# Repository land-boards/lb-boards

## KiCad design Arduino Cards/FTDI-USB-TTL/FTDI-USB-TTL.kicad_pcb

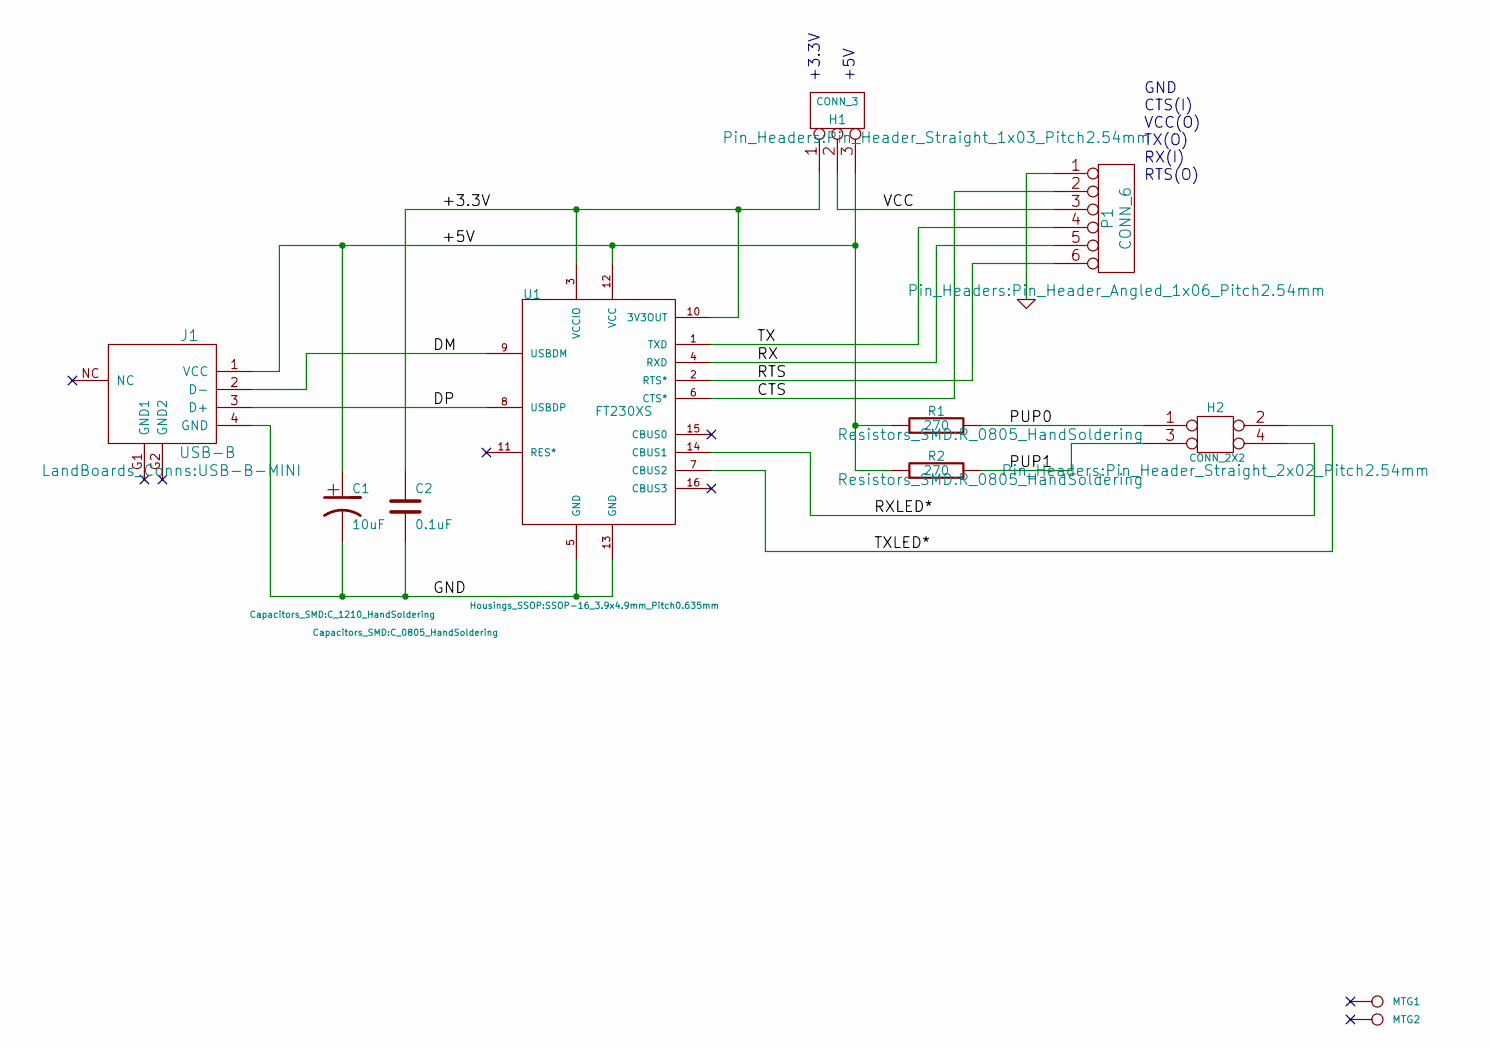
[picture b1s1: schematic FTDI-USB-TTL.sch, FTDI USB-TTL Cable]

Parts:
C1: 10uF; C_1210_HandSoldering; MfgPN CC121ZKY5V8BB106
C2: 0.1uF; C_0805_HandSoldering; MfgPN GRM155F51E104ZA1J
H1: CONN_3; Pin_Header_Straight_1x03_Pitch2.54mm; MfgPN 68002-103HLF
H2: CONN_2X2; Pin_Header_Straight_2x02_Pitch2.54mm
J1: USB-B; USB-B-MINI; MfgPN UX60SC-MB-5ST(80)
MTG1: CONN_1; MTG-4-40; MfgPN N/A
MTG2: CONN_1; MTG-4-40
P1: CONN_6; Pin_Header_Angled_1x06_Pitch2.54mm; MfgPN 68002-106HLF
R1: 270; R_0805_HandSoldering; MfgPN CRG0805F270R
R2: 270; R_0805_HandSoldering
U1: FT230XS; SSOP-16_3.9x4.9mm_Pitch0.635mm

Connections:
/+3.3V: C2.1, H1.1, U1.3 (VCCIO), U1.10 (3V3OUT)
/+5V: C1.1, H1.3, J1.1 (VCC), R1.1, R2.1, U1.12 (VCC)
/CTS: P1.2, U1.6 (CTS*)
/DM: J1.2 (D-), U1.9 (USBDM)
/DP: J1.3 (D+), U1.8 (USBDP)
/PUP0: H2.1, R1.2
/PUP1: H2.3, R2.2
/RTS: P1.6, U1.2 (RTS*)
/RX: P1.5, U1.4 (RXD)
/RXLED*: H2.4, U1.14 (CBUS1)
/TX: P1.4, U1.1 (TXD)
/TXLED*: H2.2, U1.7 (CBUS2)
/VCC: H1.2 (PM), P1.3
GND: C1.2, C2.2, J1.4 (GND), P1.1, U1.5 (GND), U1.13 (GND)

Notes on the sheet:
GND CTS(I) VCC(O) TX(O) RX(I) RTS(O)
+3.3V +5V

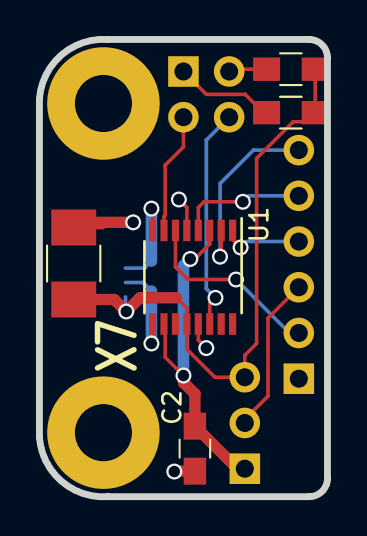
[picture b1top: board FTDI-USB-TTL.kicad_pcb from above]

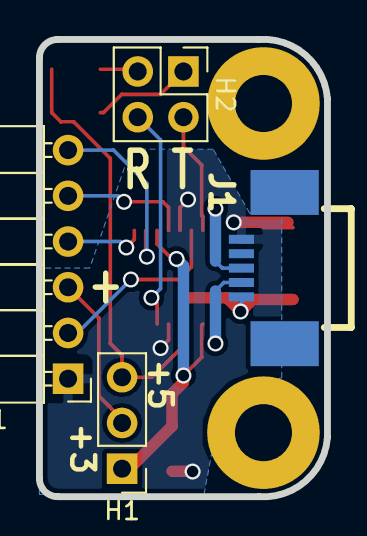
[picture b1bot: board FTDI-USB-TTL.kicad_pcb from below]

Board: 2 copper layers, 16.0 x 25.4 mm, 11 parts (4 on the bottom side), 14 nets.

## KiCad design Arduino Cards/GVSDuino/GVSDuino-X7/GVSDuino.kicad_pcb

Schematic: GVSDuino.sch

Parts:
C1, C2, C3, C6, C7: 0.1uF; C1
C4, C5: CP1; C_Radial_D5_L11_P2.5
D1: 1N4004; D4
J1: CONN_3; PIN_ARRAY_3X1
J2: DCJ0202; DCJ-NEW
J3: CONN_6X2; pin_array_6x2
J4: CONN_6; PIN_ARRAY-6X1
K1, K2, K3, K4, K5, K6, K7, K8, K9, K10, K11, K12, K13, K14, K15, K16, K17, K18, K19, K20, K21: CONN_3; PIN_ARRAY_3X1
MTG1, MTG2, MTG3, MTG4: CONN_1; MTG-4-40
R1: 10K; R4
U1: ATMEGA328-PU; DIP-28__300
U2: AP1117; SOT223
Y1: 16MHz

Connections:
+5V: C6.1, C7.1, D1.2 (K), J1.2 (PM), J3.2, K7.2 (PM), K8.2 (PM), K9.2 (PM), K10.2 (PM), K11.2 (PM), K12.2 (PM), K13.2 (PM), K14.2 (PM), K15.2 (PM), K16.2 (PM), K17.2 (PM), K18.2 (PM), K19.2 (PM), K20.2 (PM), K21.1, R1.1, U1.7 (VCC@1), U1.20 (AVCC)
/AD0: K1.3, U1.23 (PC0(ADC0))
/AD1: K2.3, U1.24 (PC1(ADC1))
/AD2: K3.3, U1.25 (PC2(ADC2))
/AD3: K4.3, U1.26 (PC3(ADC3))
/AD4: K5.3, U1.27 (PC4(ADC4/SDA))
/AD5: K6.3, U1.28 (PC5(ADC5/SCL))
/AREF: C1.1, K21.3, U1.21 (AREF)
/D0: J4.4, K7.3, U1.2 (PD0(RXD))
/D1: J4.5, K8.3, U1.3 (PD1(TXD))
/D2: K9.3, U1.4 (PD2(INT0))
/D3: K10.3, U1.5 (PD3(INT1))
/D4: K11.3, U1.6 (PD4(T0/XCK))
/D5: K12.3, U1.11 (PD5(T1))
/D6: J3.9, K13.3, U1.12 (PD6(AIN0))
/D7: J3.8, K14.3, U1.13 (PD7(AIN1))
/D8: J3.10, K15.3, U1.14 (PB0(ICP1))
/D9: J3.12, K16.3, U1.15 (PB1(OC1A))
/D10: J3.7, K17.3, U1.16 (PB2(SS/OC1B))
/D11: J3.4, K18.3, U1.17 (PB3(MOSI/OC2))
/D12: J3.1, K19.3, U1.18 (PB4(MISO))
/D13: J3.3, K20.3, U1.19 (PB5(SCK))
/FTDIRES: C2.1, J4.6
/RES0: U1.9 (PB6(XTAL1/TOSC1)), Y1.1
/RES1: U1.10 (PB7(XTAL2/TOSC2)), Y1.3
/RESET: C2.2, D1.1 (A), J3.5, R1.2, U1.1 (PC6(/RESET))
/VIN: C3.1, C4.1, J2.1, J3.11, U2.3 (VIN)
/VREG: C5.1, J1.1, U2.2 (VO), U2.4 (VO)
GND: C1.2, C3.2, C4.2, C5.2, C6.2, C7.2, J2.2, J2.3, J3.6, J4.1, J4.2, K1.1, K2.1, K3.1, K4.1, K5.1, K6.1, K7.1, K8.1, K9.1, K10.1, K11.1, K12.1, K13.1, K14.1, K15.1, K16.1, K17.1, K18.1, K19.1, K20.1, U1.8 (GND@1), U1.22 (AGND), U2.1 (GND), Y1.2
unnamed: J1.3, J4.3
unnamed: K1.2 (PM), K2.2 (PM), K3.2 (PM), K4.2 (PM), K5.2 (PM), K6.2 (PM), K21.2 (PM)

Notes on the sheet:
FTDI CONNECTOR
POWER SELECTION
ANALOG INPUTS
Voltage Selector
Power from +5V
Power from AREF
DIGITAL I/O
SPI/ATProgHead
VOLTAGE REGULATOR
Power from Regulator
Power from FTDI

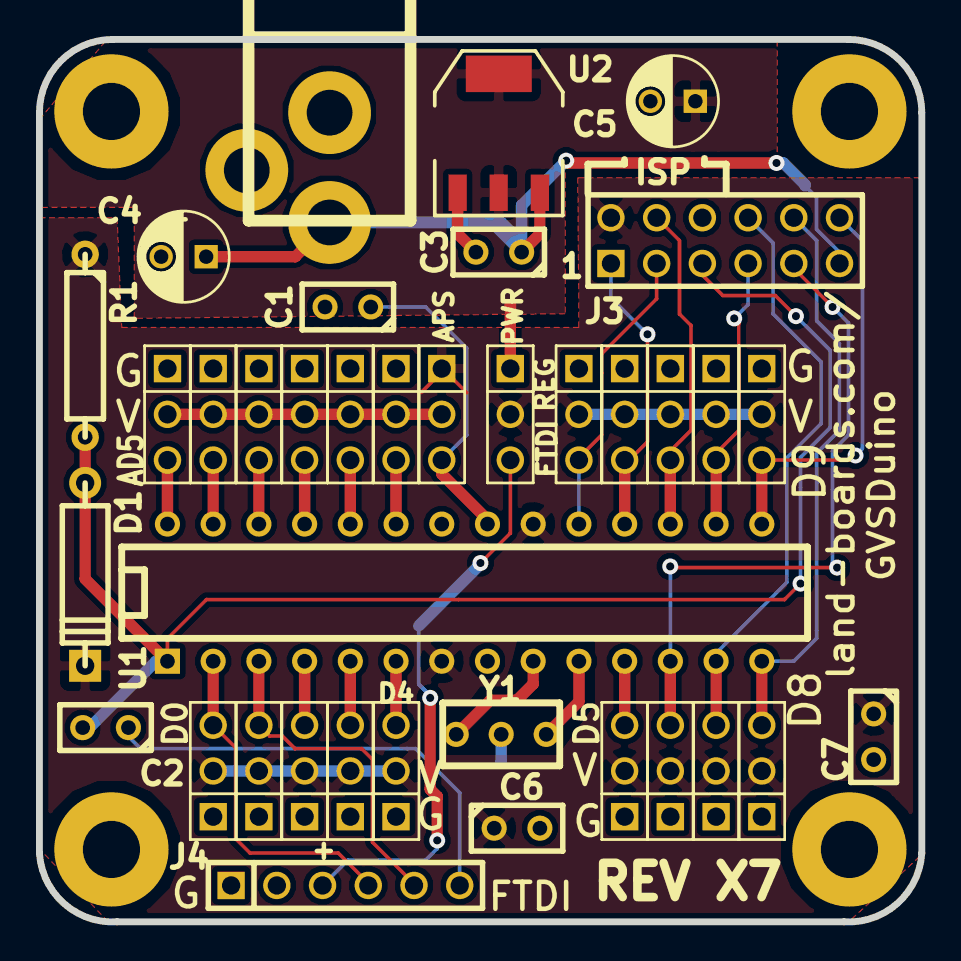
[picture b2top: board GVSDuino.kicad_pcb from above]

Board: 2 copper layers, 49.0 x 49.0 mm, 42 parts (0 on the bottom side), 31 nets.

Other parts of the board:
TESTED: VAL**; TEST_BLK-REAR

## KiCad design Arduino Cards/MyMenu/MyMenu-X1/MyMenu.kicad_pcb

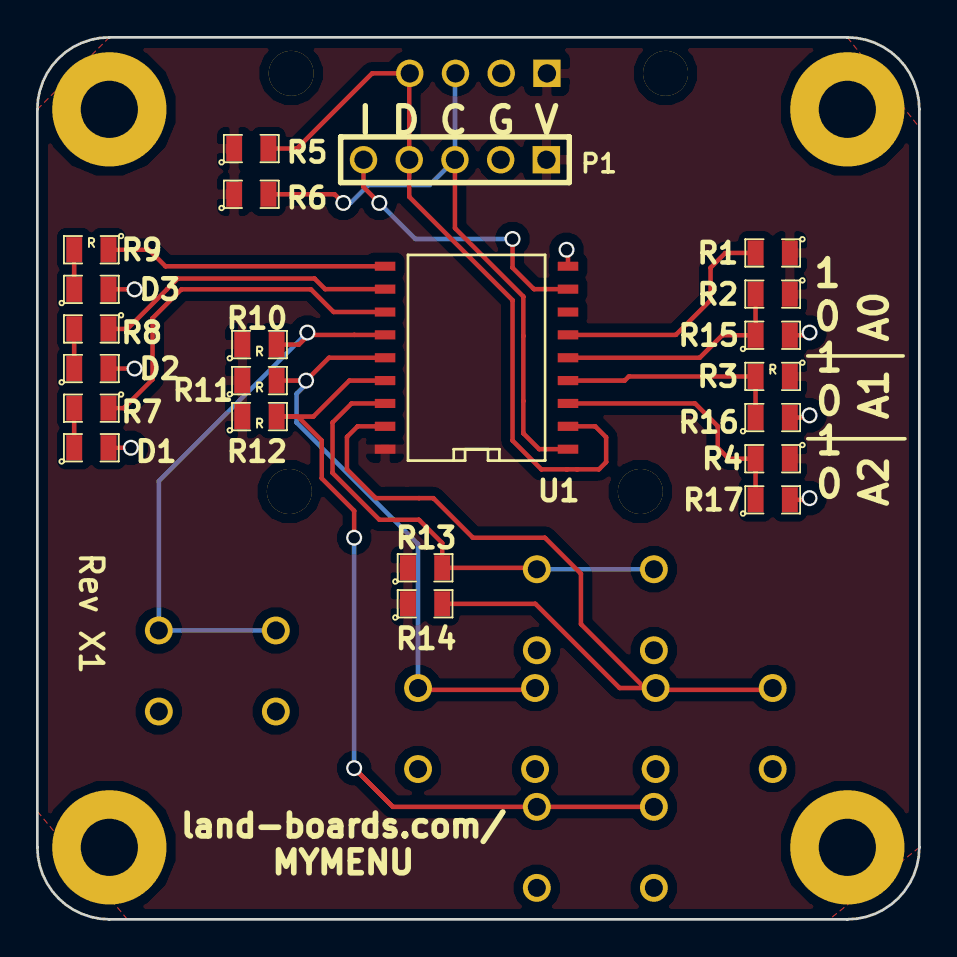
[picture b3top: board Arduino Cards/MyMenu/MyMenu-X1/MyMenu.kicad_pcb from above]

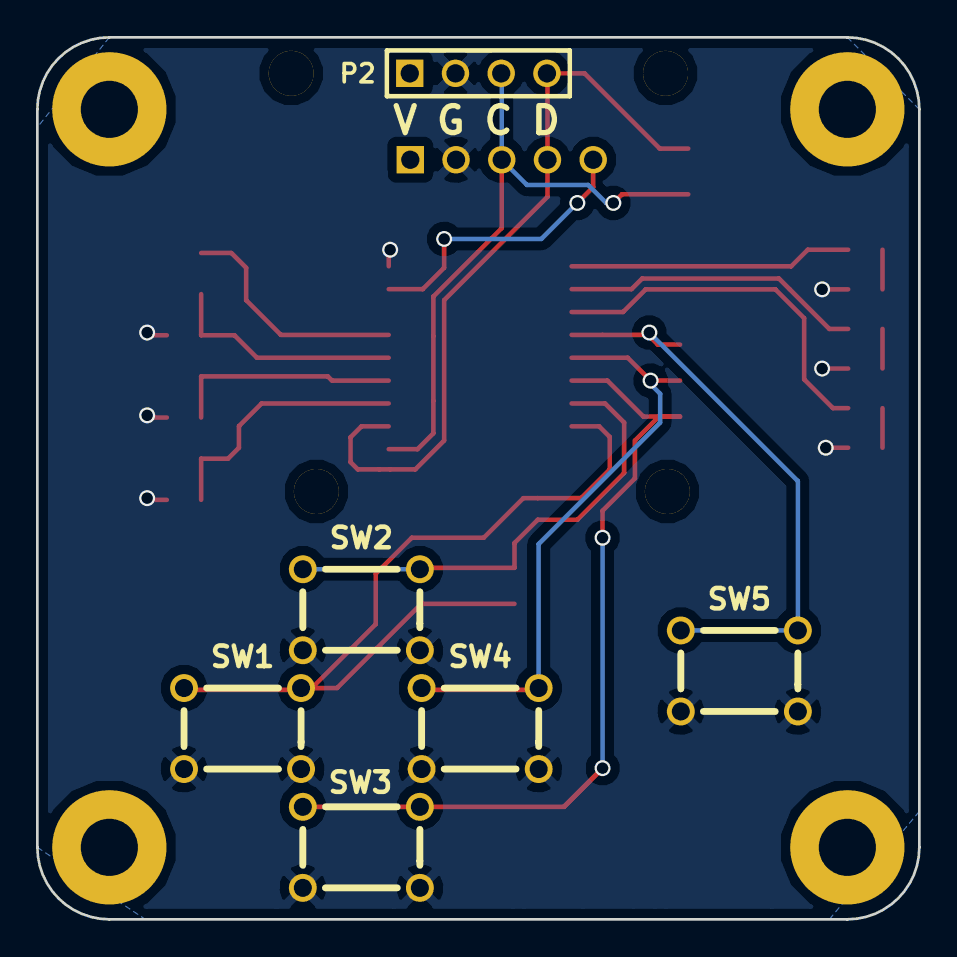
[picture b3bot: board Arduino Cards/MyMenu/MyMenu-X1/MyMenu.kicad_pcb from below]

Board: 2 copper layers, 49.0 x 49.0 mm, 36 parts (6 on the bottom side), 20 nets.

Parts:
D1, D2, D3: LED; SM0805
MTG1, MTG2, MTG3, MTG4: CONN_1; MTG-4-40
MTG5, MTG6, MTG7, MTG8: CONN_1; MTG-2.5MM
P1: CONN_5; PIN_ARRAY_5X1
P2: CONN_4; PIN_ARRAY_4X1
R1, R2, R3, R4, R5, R6, R7, R8, R9, R10, R11, R12, R13, R14, R15, R16, R17: R; SM0805
SW1, SW2, SW3, SW4, SW5: SW_PUSH_OMRON; SW-PB-6MM
U1: MCP23008SO; SO18W

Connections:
/A0: R2.2, R15.1, U1.5
/A1: R3.2, R16.1, U1.4
/A2: R4.2, R17.1, U1.3
/GND: D1.2, D2.2, D3.2, P1.2, P2.2, R15.2, R16.2, R17.2, SW1.3, SW1.4, SW2.3, SW2.4, SW3.3, SW3.4, SW4.3, SW4.4, SW5.3, SW5.4, U1.9
/SCL: P1.3, P2.3, R6.2, U1.1
/SDA: P1.4, P2.4, R5.2, U1.2
/VCC: P1.1, P2.1, R1.1, R2.1, R3.1, R4.1, R5.1, R6.1, R10.1, R11.1, R12.1, R13.1, R14.1, U1.18
unnamed: D1.1, R7.2
unnamed: R8.1, U1.11
unnamed: D2.1, R8.2
unnamed: D3.1, R9.2
unnamed: R7.1, U1.12
unnamed: R1.2, U1.6
unnamed: R9.1, U1.10
unnamed: P1.5, U1.8
unnamed: R14.2, SW1.1, SW1.2, U1.17
unnamed: R13.2, SW2.1, SW2.2, U1.16
unnamed: R12.2, SW3.1, SW3.2, U1.15
unnamed: R11.2, SW4.1, SW4.2, U1.14
unnamed: R10.2, SW5.1, SW5.2, U1.13

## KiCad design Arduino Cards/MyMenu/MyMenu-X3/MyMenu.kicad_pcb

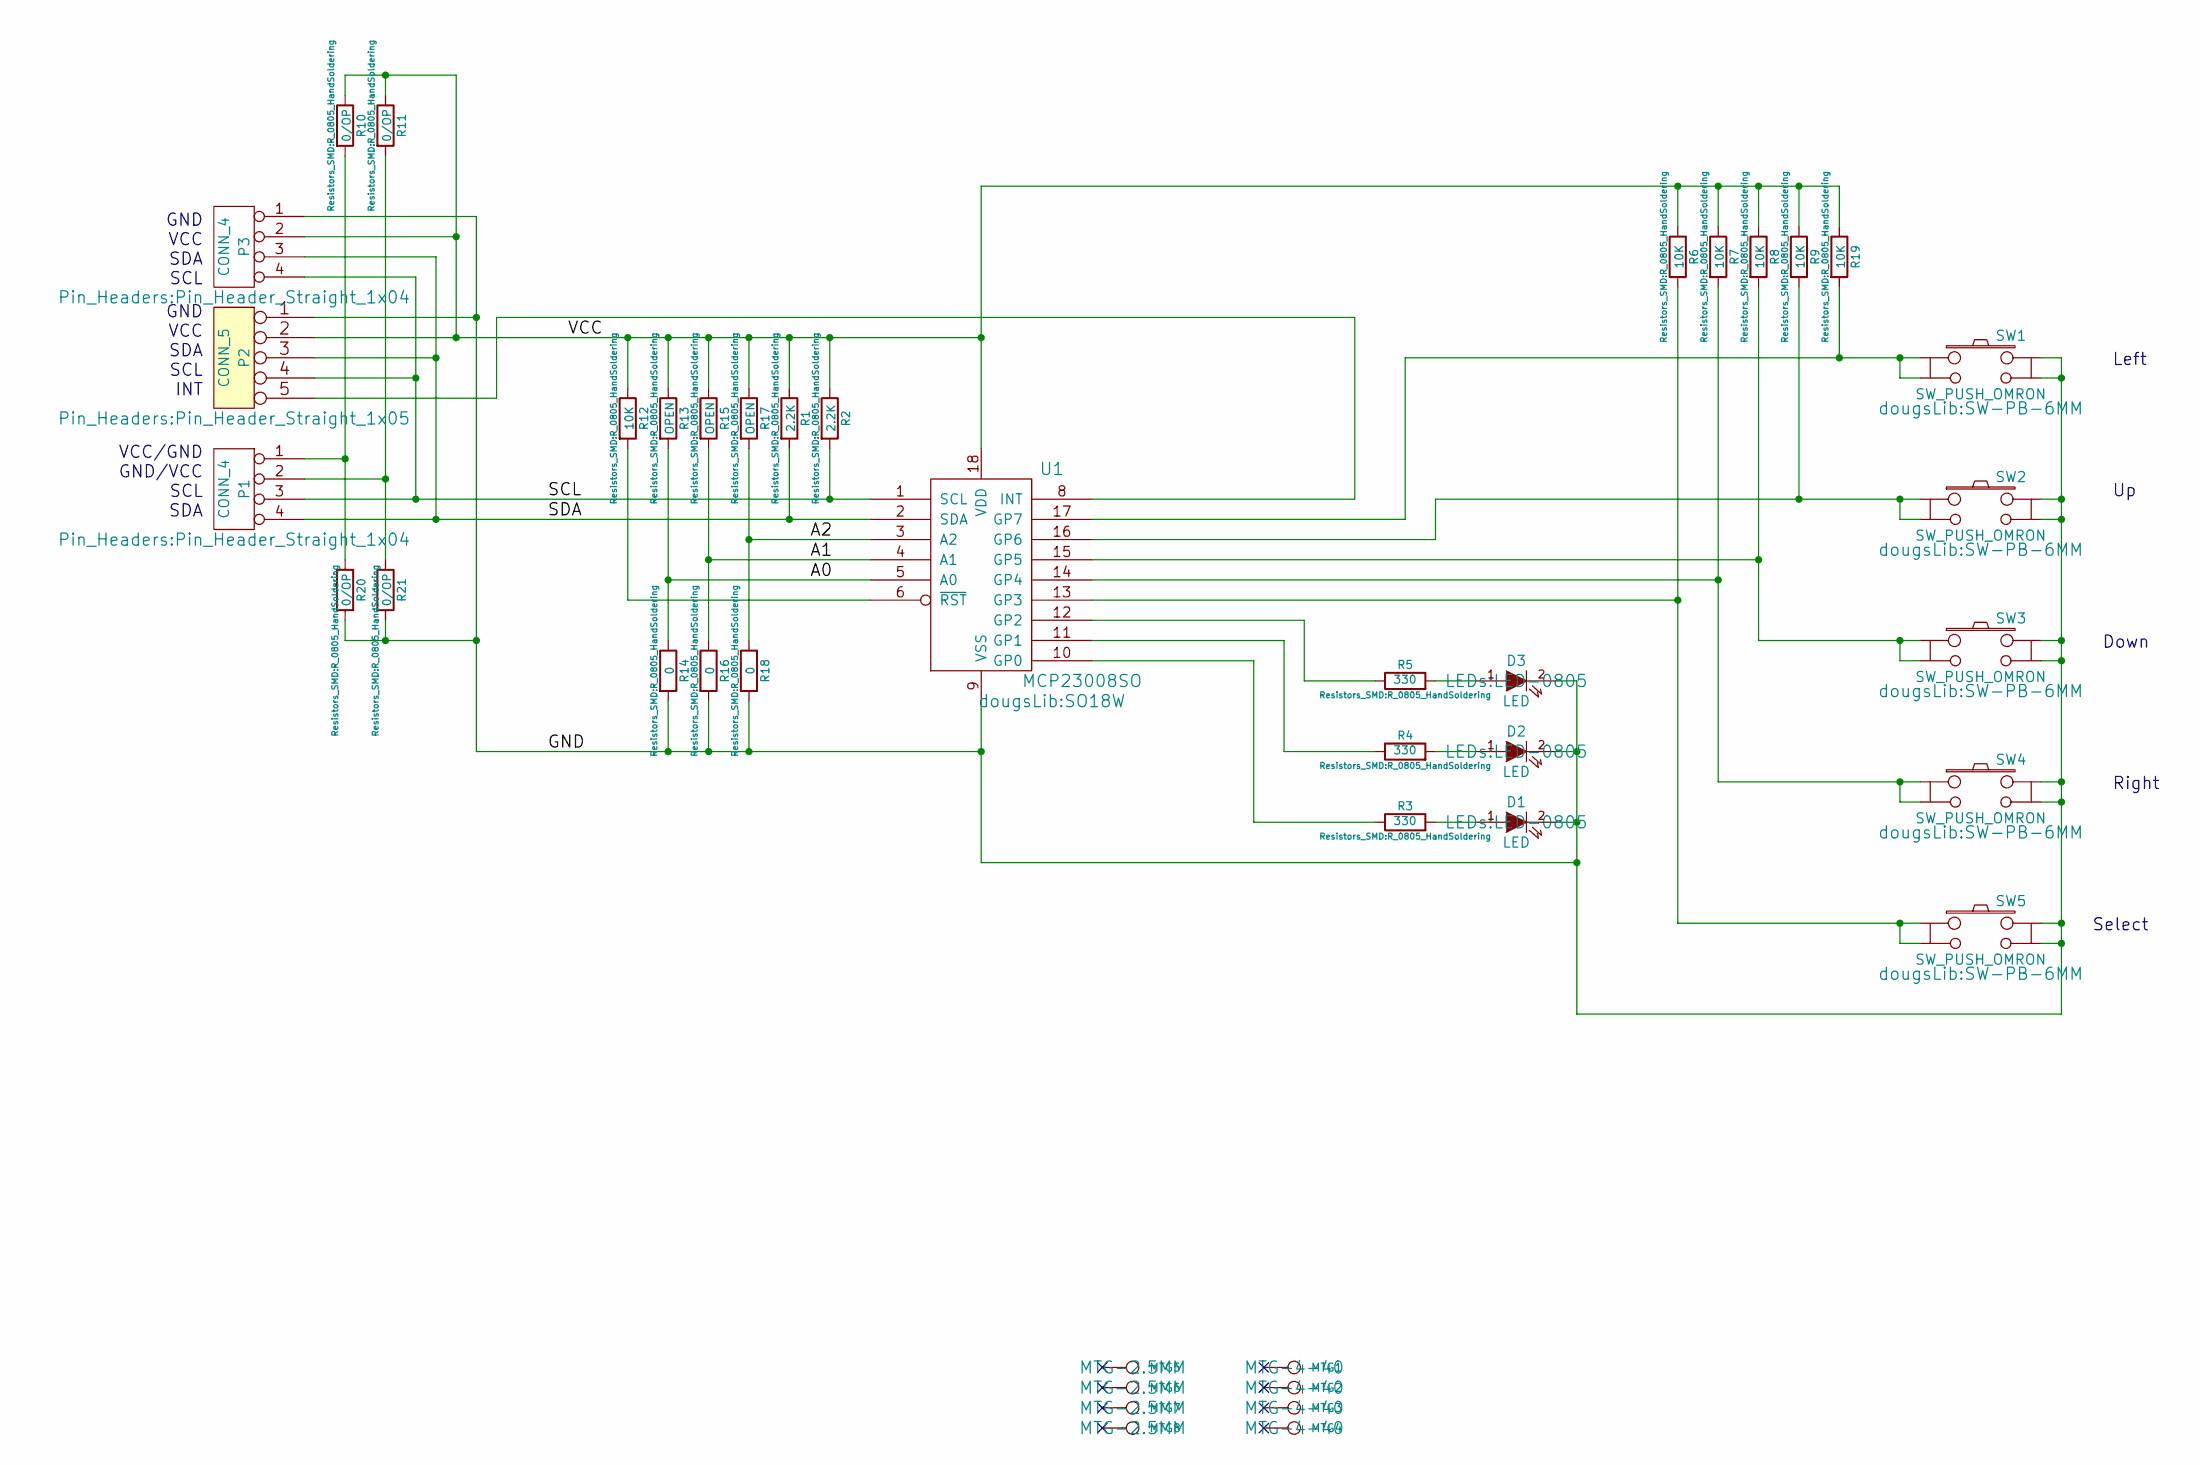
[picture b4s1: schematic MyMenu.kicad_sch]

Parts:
D1, D2, D3: LED; LED-0805
MTG1, MTG2, MTG3, MTG4: CONN_1; MTG-4-40
MTG5, MTG6, MTG7, MTG8: CONN_1; MTG-2.5MM
P1, P3: CONN_4; Pin_Header_Straight_1x04
P2: CONN_5; Pin_Header_Straight_1x05
R1, R2: 2.2K; R_0805_HandSoldering
R3, R4, R5: 330; R_0805_HandSoldering
R6, R7, R8, R9, R12, R19: 10K; R_0805_HandSoldering
R10, R11, R20, R21: 0/OP; R_0805_HandSoldering
R13, R15, R17: OPEN; R_0805_HandSoldering
R14, R16, R18: 0; R_0805_HandSoldering
SW1, SW2, SW3, SW4, SW5: SW_PUSH_OMRON; SW-PB-6MM
U1: MCP23008SO; SO18W

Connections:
/A0: R13.2, R14.1, U1.5 (A0)
/A1: R15.2, R16.1, U1.4 (A1)
/A2: R17.2, R18.1, U1.3 (A2)
/GND: D1.2 (K), D2.2 (K), D3.2 (K), P2.1, P3.1, R14.2, R16.2, R18.2, R20.2, R21.2, SW1.3, SW1.4, SW2.3, SW2.4, SW3.3, SW3.4, SW4.3, SW4.4, SW5.3, SW5.4, U1.9 (VSS)
/SCL: P1.3, P2.4, P3.4, R2.2, U1.1 (SCL)
/SDA: P1.4, P2.3, P3.3, R1.2, U1.2 (SDA)
/VCC: P2.2, P3.2, R1.1, R2.1, R6.1, R7.1, R8.1, R9.1, R10.1, R11.1, R12.1, R13.1, R15.1, R17.1, R19.1, U1.18 (VDD)
unnamed: D1.1 (A), R3.2
unnamed: D2.1 (A), R4.2
unnamed: D3.1 (A), R5.2
unnamed: P1.1, R10.2, R20.1
unnamed: P1.2, R11.2, R21.1
unnamed: P2.5, U1.8 (INT)
unnamed: R3.1, U1.10 (GP0)
unnamed: R4.1, U1.11 (GP1)
unnamed: R5.1, U1.12 (GP2)
unnamed: R6.2, SW5.1, SW5.2, U1.13 (GP3)
unnamed: R7.2, SW4.1, SW4.2, U1.14 (GP4)
unnamed: R8.2, SW3.1, SW3.2, U1.15 (GP5)
unnamed: R9.2, SW2.1, SW2.2, U1.16 (GP6)
unnamed: R12.2, U1.6 (~RST)
unnamed: R19.2, SW1.1, SW1.2, U1.17 (GP7)

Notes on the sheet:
GND VCC SDA SCL
Left
GND VCC SDA SCL INT
Select
Right
VCC/GND GND/VCC SCL SDA
Down

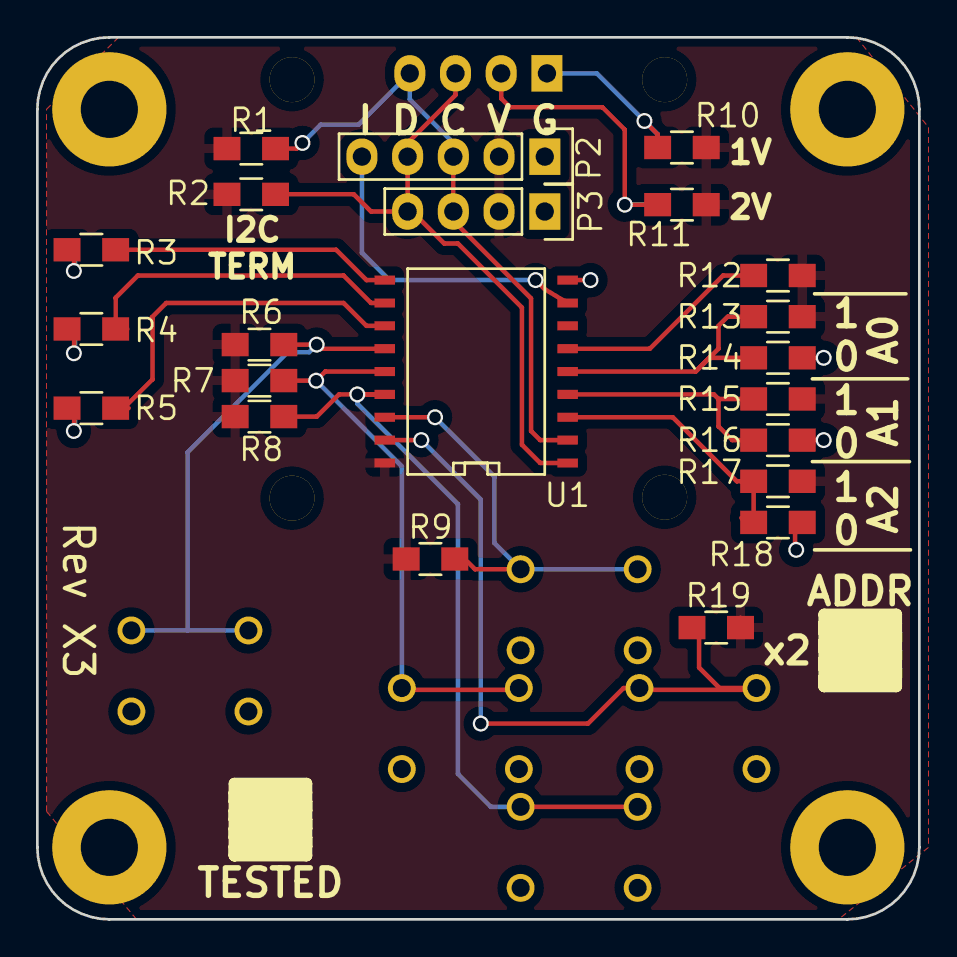
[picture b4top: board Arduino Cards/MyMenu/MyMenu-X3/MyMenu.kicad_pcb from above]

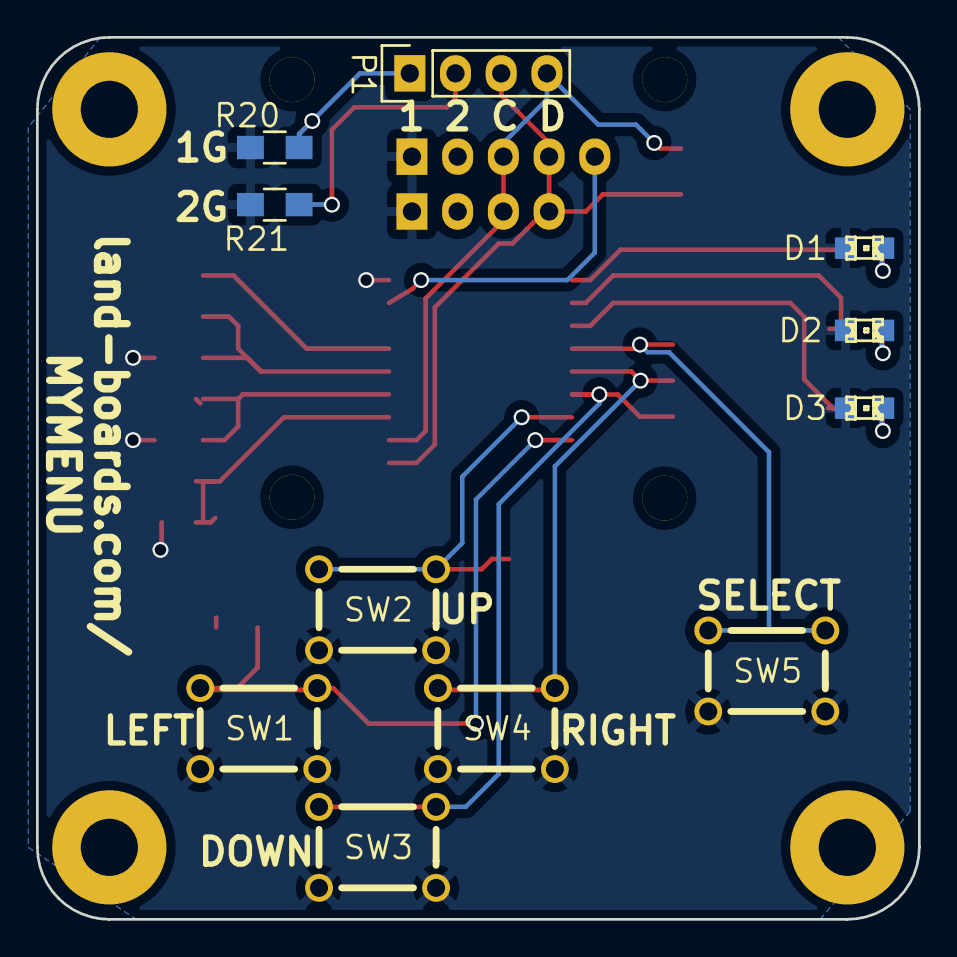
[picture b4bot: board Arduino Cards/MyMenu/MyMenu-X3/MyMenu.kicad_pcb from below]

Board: 2 copper layers, 49.0 x 49.0 mm, 43 parts (13 on the bottom side), 22 nets.

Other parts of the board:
ADDR: VAL**; TEST_BLK-REAR
TESTED: VAL**; TEST_BLK-REAR

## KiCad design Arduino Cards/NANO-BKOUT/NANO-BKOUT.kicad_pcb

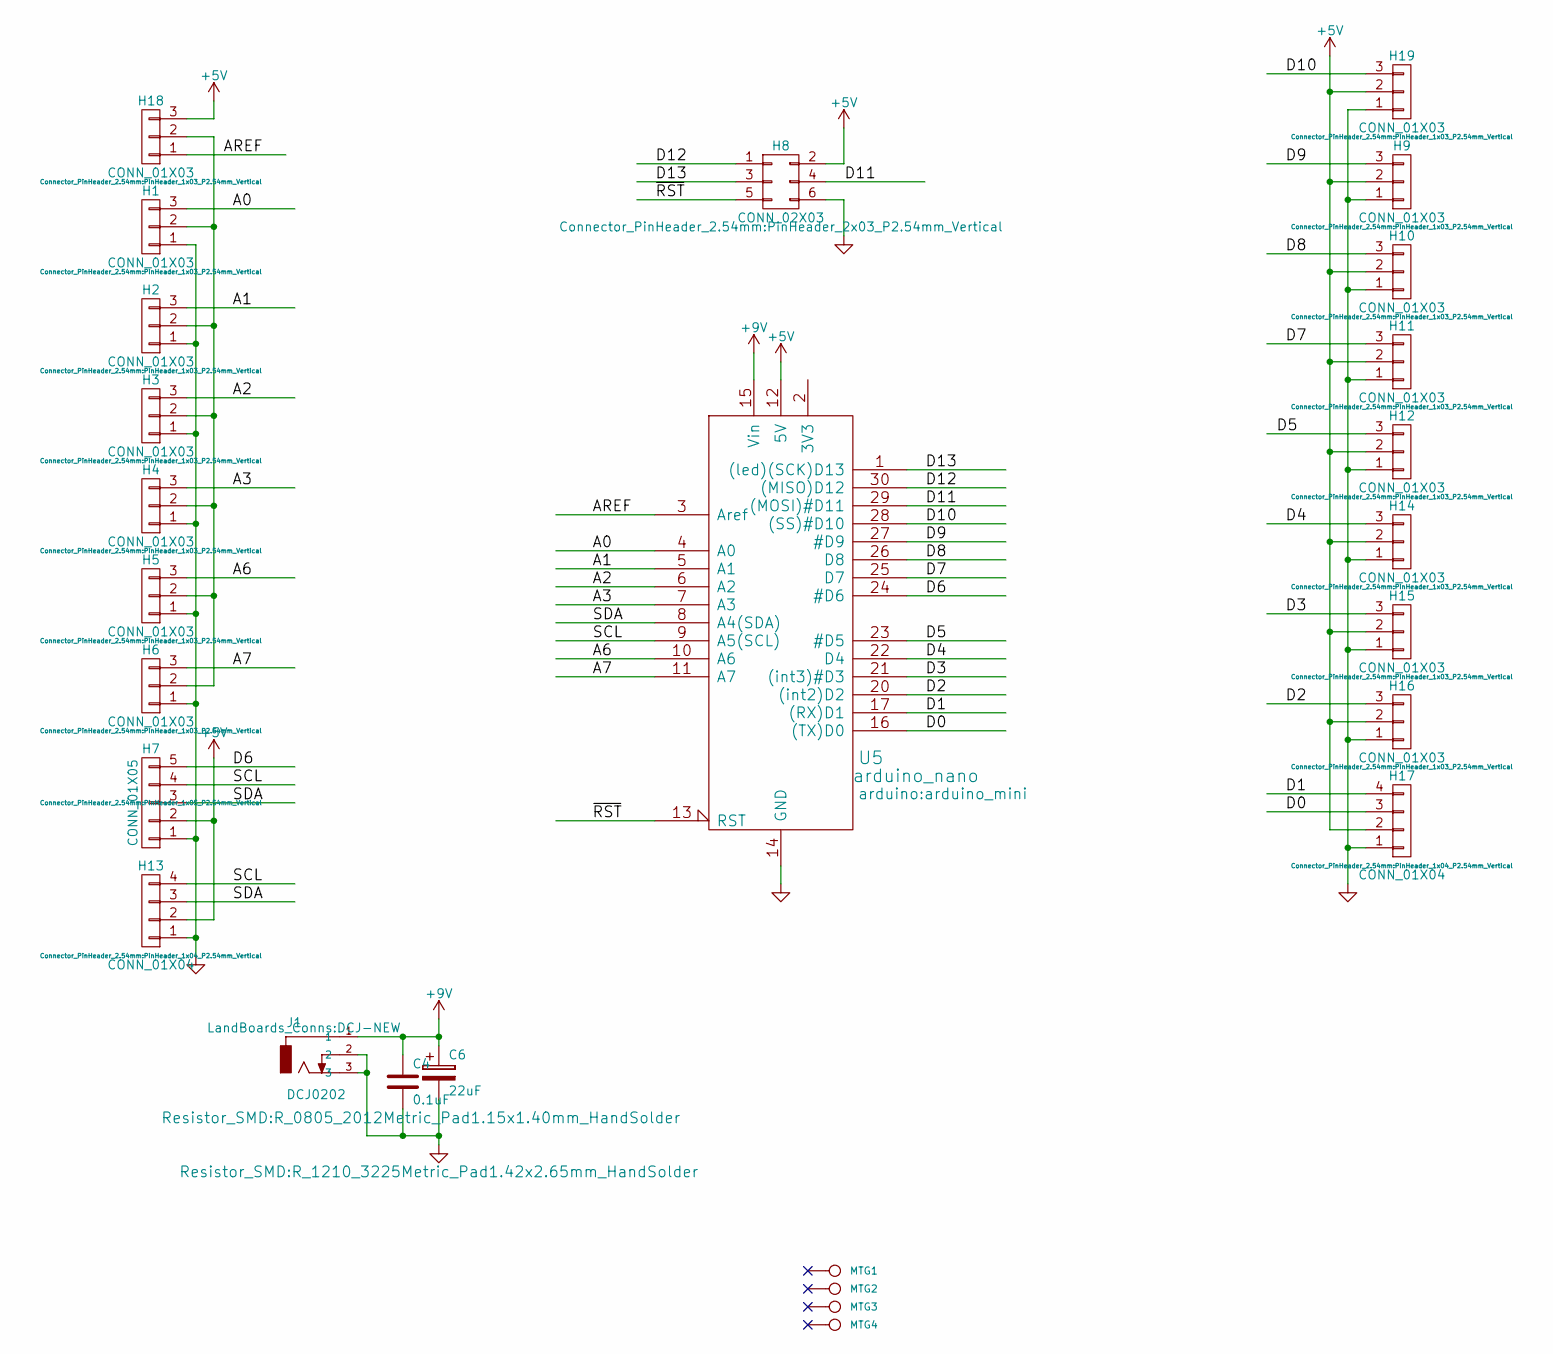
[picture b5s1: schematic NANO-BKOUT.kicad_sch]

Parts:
C4: 0.1uF; R_0805_2012Metric_Pad1.15x1.40mm_HandSolder
C6: 22uF; R_1210_3225Metric_Pad1.42x2.65mm_HandSolder
H1, H2, H3, H4, H5, H6, H9, H10, H11, H12, H14, H15, H16, H18, H19: CONN_01X03; PinHeader_1x03_P2.54mm_Vertical
H7: CONN_01X05; PinHeader_1x05_P2.54mm_Vertical
H8: CONN_02X03; PinHeader_2x03_P2.54mm_Vertical
H13, H17: CONN_01X04; PinHeader_1x04_P2.54mm_Vertical
J1: DCJ0202; DCJ-NEW
MTG1, MTG2, MTG3, MTG4: CONN_1; MTG-4-40
U5: arduino_nano; arduino_mini

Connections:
+5V: H7.2, H8.2, H9.2, H10.2, H11.2, H12.2, H13.2, H14.2, H15.2, H16.2, H17.2, H18.3, H19.2, U5.12 (5V)
+9V: C4.1, C6.1, J1.1, U5.15 (Vin)
/A0: H1.3, U5.4 (A0)
/A1: H2.3, U5.5 (A1)
/A2: H3.3, U5.6 (A2)
/A3: H4.3, U5.7 (A3)
/A6: H5.3, U5.10 (A6)
/A7: H6.3, U5.11 (A7)
/AREF: H18.1, U5.3 (Aref)
/D0: H17.3, U5.16 ((TX)D0)
/D1: H17.4, U5.17 ((RX)D1)
/D2: H16.3, U5.20 ((int2)D2)
/D3: H15.3, U5.21 ((int3)#D3)
/D4: H14.3, U5.22 (D4)
/D5: H12.3, U5.23 (#D5)
/D6: H7.5, U5.24 (#D6)
/D7: H11.3, U5.25 (D7)
/D8: H10.3, U5.26 (D8)
/D9: H9.3, U5.27 (#D9)
/D10: H19.3, U5.28 ((SS)#D10)
/D11: H8.4, U5.29 ((MOSI)#D11)
/D12: H8.1, U5.30 ((MISO)D12)
/D13: H8.3, U5.1 ((led)(SCK)D13)
/SCL: H7.4, H13.4, U5.9 (A5(SCL))
/SDA: H7.3, H13.3, U5.8 (A4(SDA))
/~RST: H8.5, U5.13 (RST)
GND: C4.2, C6.2, H1.1, H2.1, H3.1, H4.1, H5.1, H6.1, H7.1, H8.6, H9.1, H10.1, H11.1, H12.1, H13.1, H14.1, H15.1, H16.1, H17.1, H19.1, J1.2, J1.3, U5.14 (GND), U5.19 (GND)
unnamed: H1.2, H2.2, H3.2, H4.2, H5.2, H6.2, H18.2

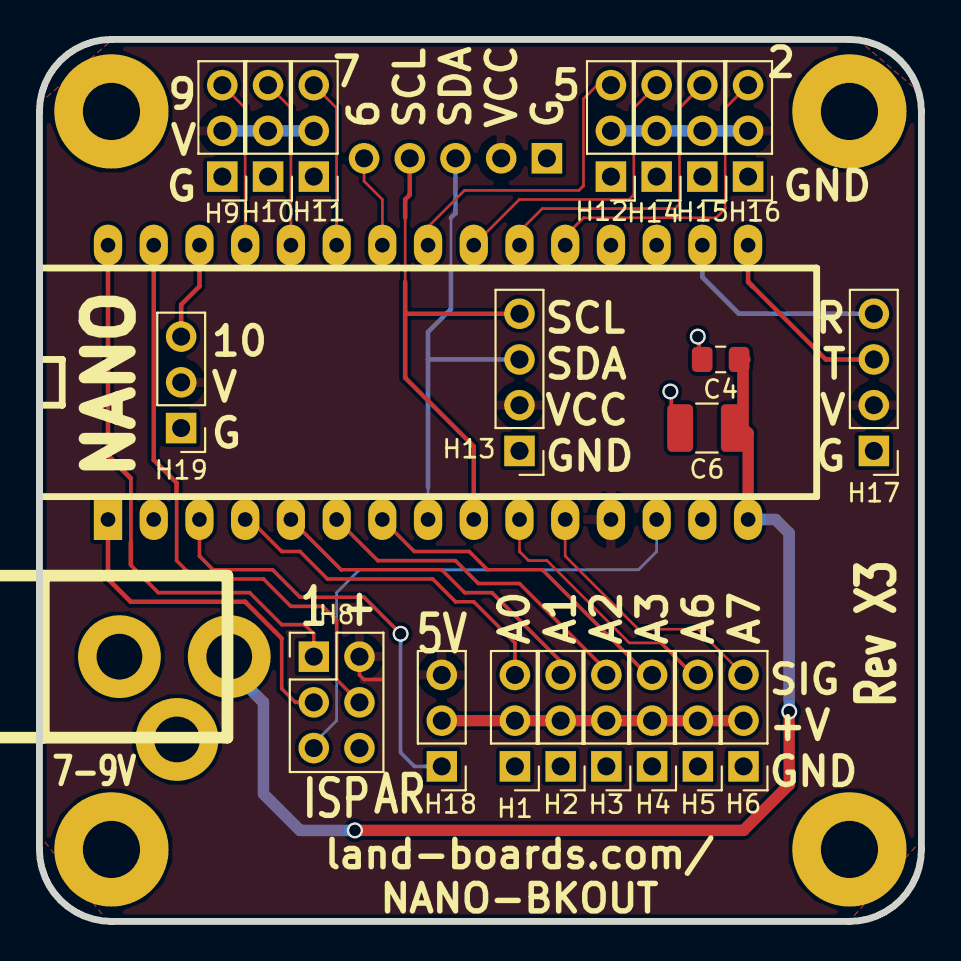
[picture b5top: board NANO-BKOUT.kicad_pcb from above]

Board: 2 copper layers, 49.0 x 49.0 mm, 27 parts (1 on the bottom side), 28 nets.
